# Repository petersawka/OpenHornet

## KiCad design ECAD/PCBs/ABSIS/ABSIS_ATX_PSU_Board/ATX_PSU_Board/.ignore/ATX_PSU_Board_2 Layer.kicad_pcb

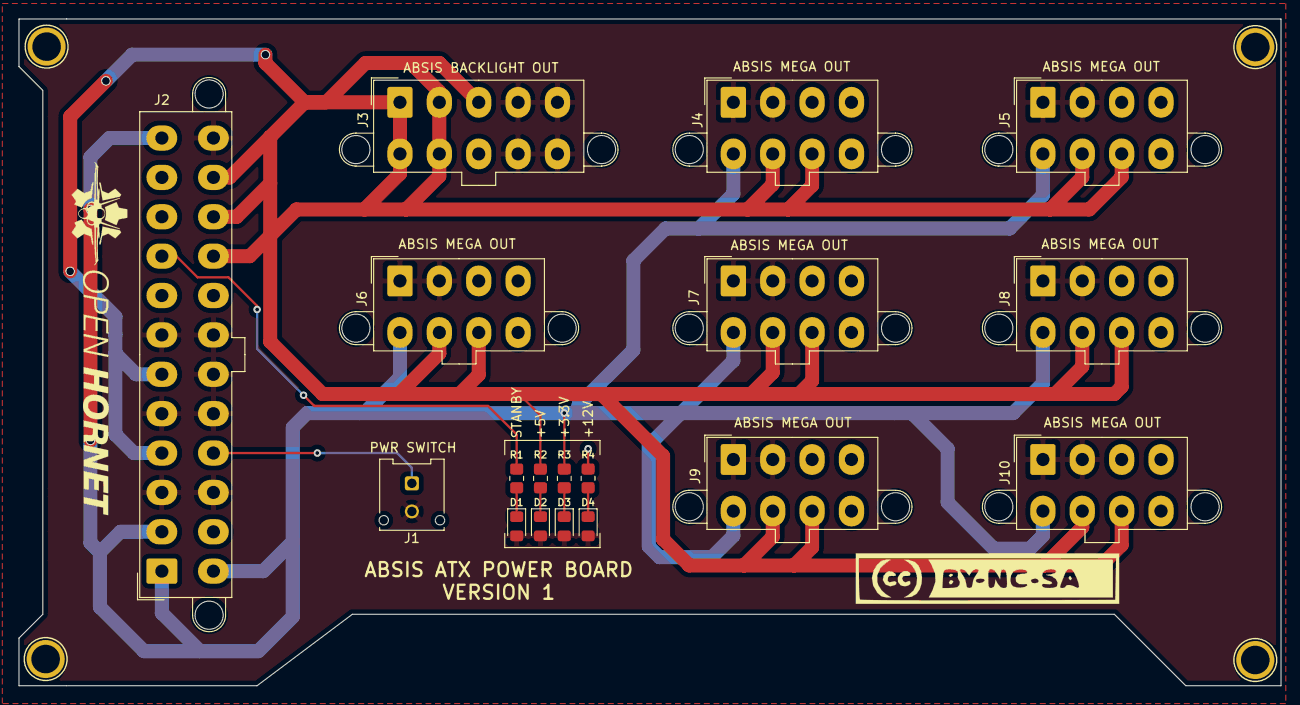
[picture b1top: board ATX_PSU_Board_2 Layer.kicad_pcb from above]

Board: 2 copper layers, 134.6 x 71.1 mm, 22 parts (0 on the bottom side), 10 nets.

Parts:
D1, D2, D3, D4: Green LED; LED_0805_2012Metric_Pad1.15x1.40mm_HandSolder
H1, H2, H3, H4: MountingHole; Arduino_1pin
J1: Power Swtich; Molex_Micro-Fit_3.0_43045-0212_2x01_P3.00mm_Vertical
J2: ATX-24; Molex_Mini-Fit_Jr_5566-24A2_2x12_P4.20mm_Vertical
J3: ABSIS BACKLIGHT PWR; Molex_Mini-Fit_Jr_5566-10A2_2x05_P4.20mm_Vertical
J4, J5, J6, J7, J8, J9, J10: MEGA BUS POWER; Molex_Mini-Fit_Jr_5566-08A2_2x04_P4.20mm_Vertical
R1, R2: 150; R_0805_2012Metric_Pad1.20x1.40mm_HandSolder
R3: 56; R_0805_2012Metric_Pad1.20x1.40mm_HandSolder
R4: 560; R_0805_2012Metric_Pad1.20x1.40mm_HandSolder

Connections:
/+3.3V_SUPPLY: J2.1, J2.2, J2.12, J2.13, J4.5, J5.5, J6.5, J7.5, J8.5, J9.5, J10.5, R3.2
/+5VSB_SUPPLY: J2.9, R1.2
/+5V_SUPPLY: J2.4, J2.6, J2.21, J2.22, J2.23, J3.1, J3.2, J3.3, J3.6, J3.7, J4.6, J4.7, J5.6, J5.7, J6.6, J6.7, J7.6, J7.7, J8.6, J8.7, J9.6, J9.7, J10.6, J10.7, R2.2
/+12V_SUPPLY: J2.10, J2.11, J3.8, J4.3, J4.4, J4.8, J5.3, J5.4, J5.8, J6.3, J6.4, J6.8, J7.3, J7.4, J7.8, J8.3, J8.4, J8.8, J9.3, J9.4, J9.8, J10.3, J10.4, J10.8, R4.2
/PS_ON: J1.1, J2.16
GND: D1.2, D2.2, D3.2, D4.2, J1.2, J2.3, J2.5, J2.7, J2.15, J2.17, J2.18, J2.19, J2.24, J3.4, J3.5, J3.9, J3.10, J4.1, J4.2, J5.1, J5.2, J6.1, J6.2, J7.1, J7.2, J8.1, J8.2, J9.1, J9.2, J10.1, J10.2
unnamed: D1.1, R1.1
unnamed: D2.1, R2.1
unnamed: D3.1, R3.1
unnamed: D4.1, R4.1

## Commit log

2020-11-13 0805 LEDs
